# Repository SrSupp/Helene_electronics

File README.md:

Author: Sven Suppelt, Felix Herbst		Date: 09.05.2023

# HELENE - electronics for the low cost 6DOF robot
This repository is responsible for the electronics for the Helene robotarm. Included are the PCBs and the code to run on these. 

The robot arm has a motor control board on each of its 6 axes. The board of the lowest axis, the 1st axis, acts as ROS Serial Slave. All other axes receive their control data from the 1st axis via CAN. 

A single motor control board consists of a microcontroller (ESP32), a stepper motor driver (TMC5160), a magnetic encoder to determine the current position of the robot arm (AS5048) and a CAN transceiver. 
The 1st axis is equipped with an external magnetic encoder due to lack of space. All other axes have enough space so that the board can be mounted directly above the required magnet. 

# Folder structure
The boards are located in the folder "pcb". Here you will find the board for the external encoder and the motor control board. The source code for the boards can be found in the "code" folder. Stored there are the PlatformIO projects for the ROS Serial Slave (Helene_ESP_Master) and the other boards connected via CAN (Helene_ESP_Slave).
In the pcb folder there are two additional optional boards, the end effector board and a H-bridge with voltage converter. The end effector board has its own ESP32 with an ADC for measuring load cells. Furthermore, two outputs for servos are provided, so that grippers with integrated force measurement can be realized. The H-bridge is connected via the expansion ports on the boards and can drive motors up to 3A at 5V. It does not have its own microcontroller.

# System structure of the robot arm

# Available Serial Commands
Each slave is equipped with the possibility of serial communication. Via this interface the calibration value of each axis can be read and set and status information can be read out. It is absolutely necessary to calibrate each axis individually!
The following commands are available:

long form | short form | description
-------- | -------- | --------
*IDN? | IDN? | Prints identification
HELP? | HELP | Prints a help screen (not yet implemented)
CALSINGLEJOINT [joint ID] | CAJO [joint ID] | starts the calibration process of given joint. Instructions will be printed after that command!
SETNULL [0,1] | SENU [0,1] | globally enables (1) or disables (0) the Nullpunktfahrt at startup
GETCALVALUE [joint ID] | GECA [joint ID] | Prints the current saved calibration value of given joint
SETCALVALUE [joint ID] | SECA [joint ID] | Sets the current saved calibration value of given joint. Instructions are printed after that command!
GETACTUAL [joint ID] | GEAC [joint ID] | Prints the actual angle of given joint. The actual angle is: Raw_Angle - Calibration_Value
GETRAW [joint ID] | GERA [joint ID] | Prints the raw angle of given joint
DONULL [joint ID] | DONU [joint ID] | The given joint will do a Nullpunktfahrt
OFFANDNULL [joint ID] | OFNU [joint ID] | Sets a offset value on the current calibration value. After that a Nullpunktfahrt is initiated. Instructions are printed out!
DIAG | DIA | Prints out diagnose data

# Installation instructions

1. Gather all materials.
You will need 6 motor control boards and 1 external encoder board.
2. Do the wiring. 
You will have to run CAN and power to each motor control board. The boards are daisy-chainable!
3. Program the boards.
"Helene_ESP_Master" should be uploaded to the board in joint 1. This board is configured with rosserial so that it communicates directly with ROS.
"Helene_ESP_Slave" should be uploaded to the boards in joint 2-6. These boards talk via CAN to the board in Joint 1 and thus receive their control information. With each individual board it is possible to calibrate the robot arm. 
After programming, each board should slowly blink red!
4. Set the SMD-Jumpers.
For joints 1 and 6 the CAN terminating resistor must be set by bridging the SMD solder bridge next to the CAN sockets.
Additionally the Joint-ID must be set for each board. For this purpose four SMD pads are provided next to the USB socket. By bridging these pads the ID can be set. The data format is binary with the most significant bit first. For example the joint 5: 0 1 0 1 must be set. 
5. Calibrate the zero position
6. Enable Nullpunktfahrt globally

# Video installation instructions

The installation process is also explained in the following video.

Starting at 0:09 the installation of the electronics is explained. From 6:21 on the calibration is shown.

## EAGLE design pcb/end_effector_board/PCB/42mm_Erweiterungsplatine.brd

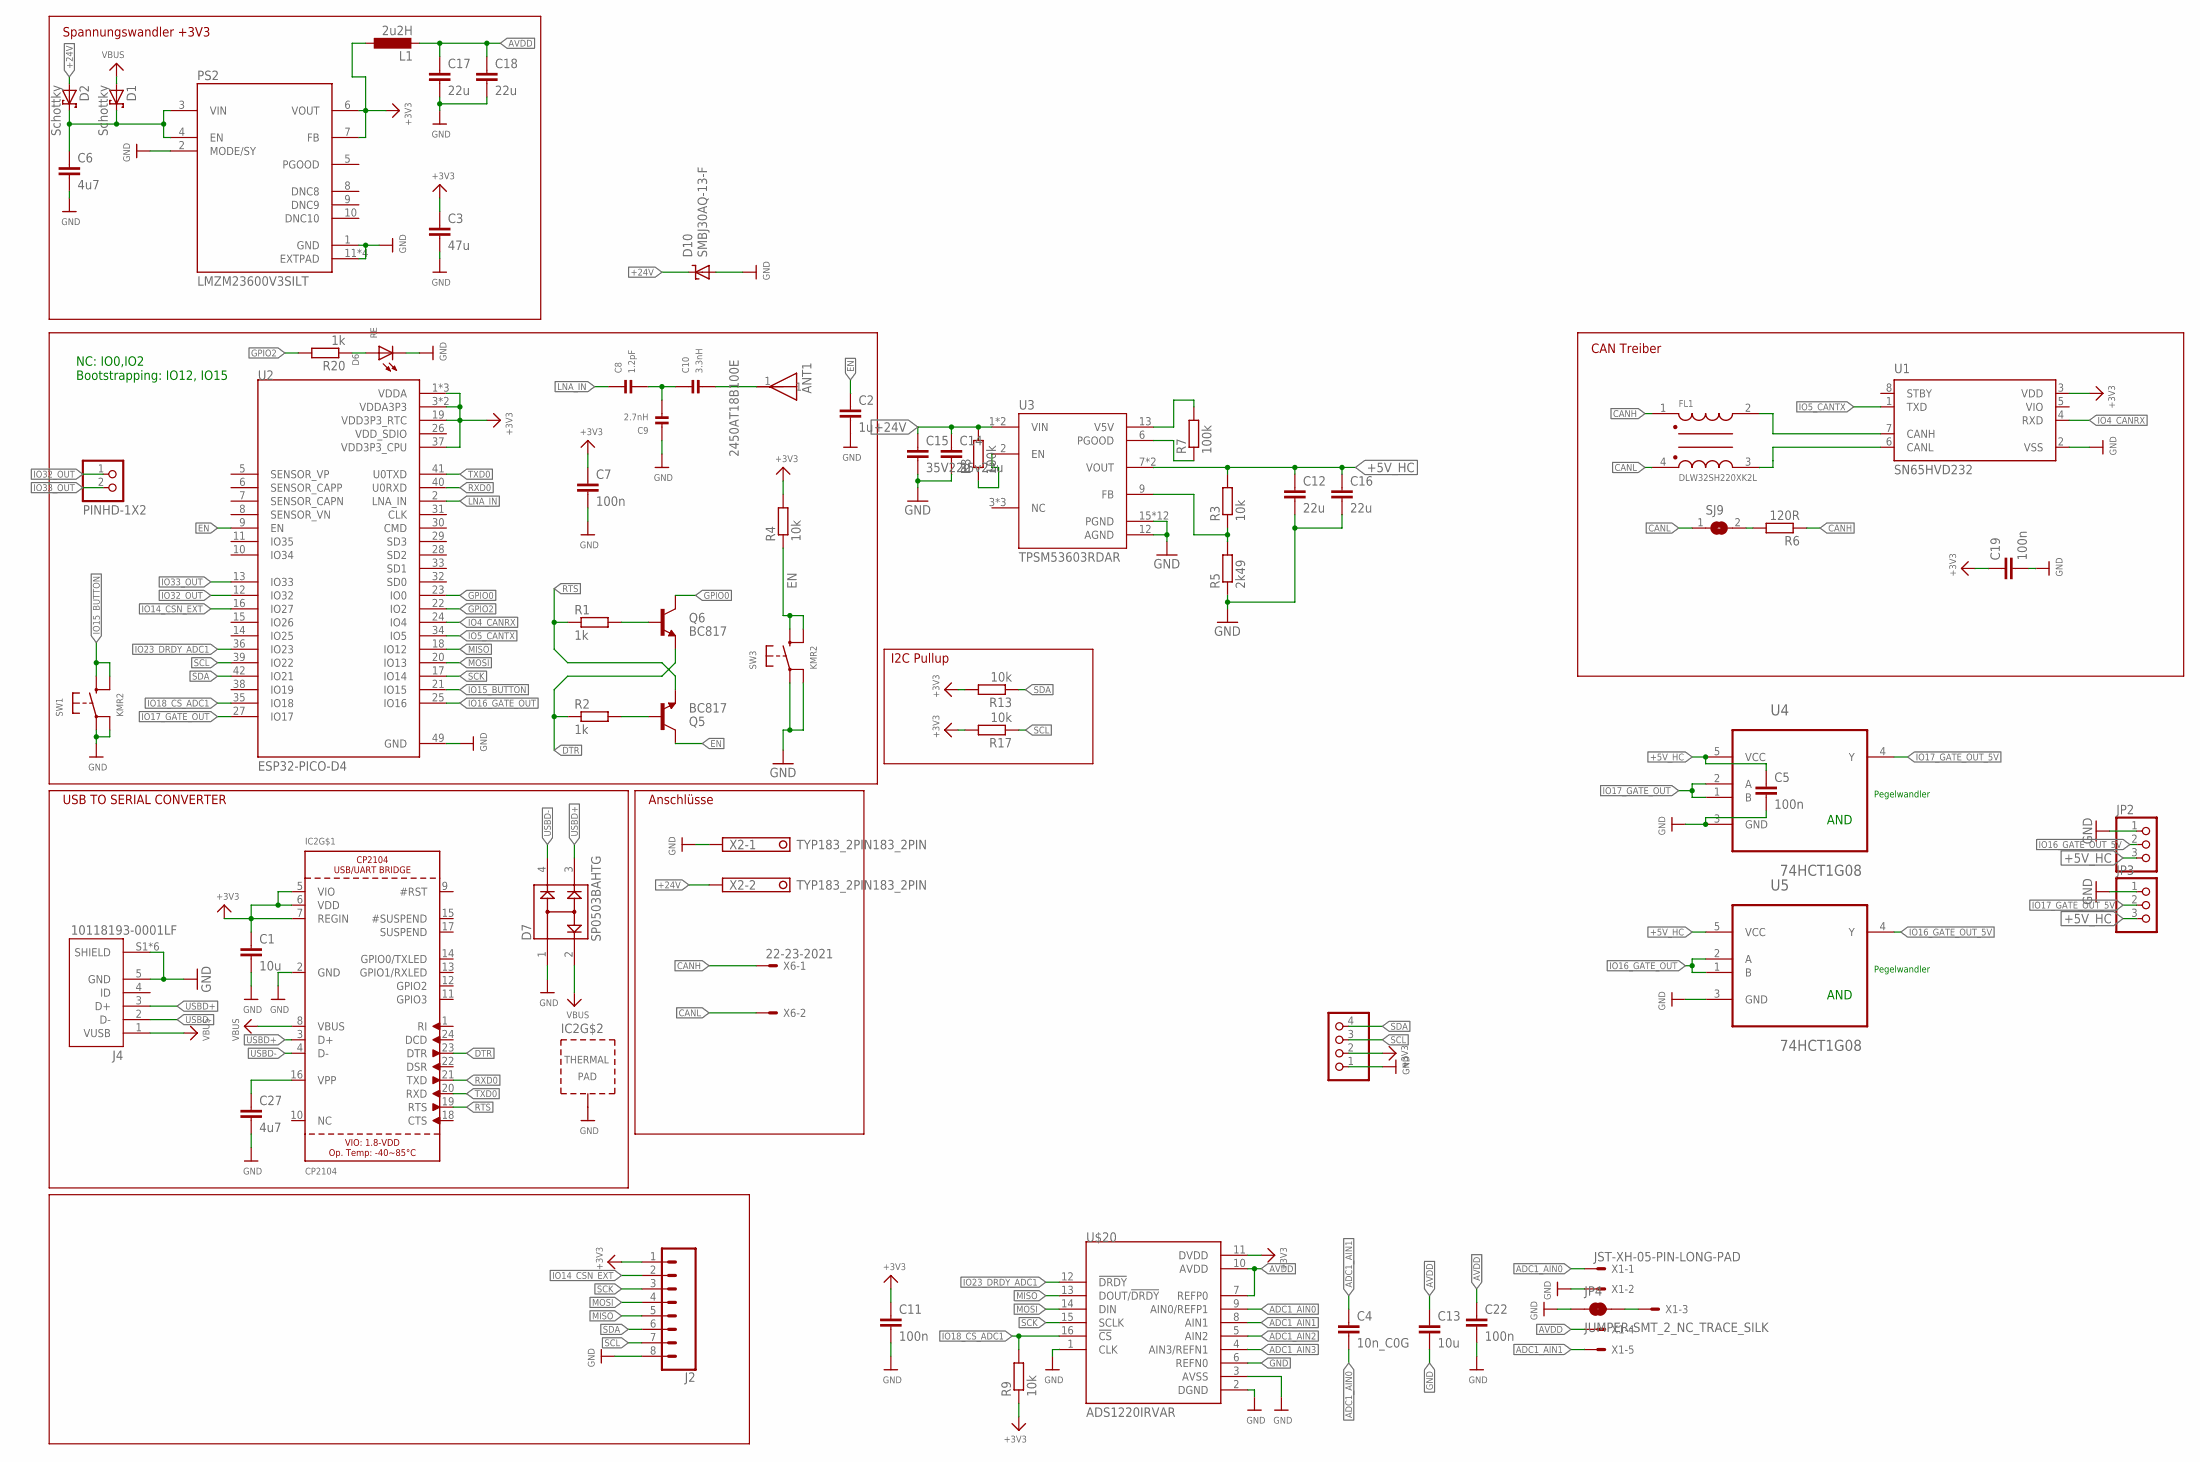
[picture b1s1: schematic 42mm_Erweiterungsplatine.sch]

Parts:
ANT1: 2450AT18B100E; ANT_2450AT18B100E
C1, C13: 10u; C0805
C2: 1u; C0805
C3: 47u; C0805
C4: 10n_C0G; C0805
C5, C7, C11, C19, C22: 100n; C0805
C6, C27: 4u7; C0805
C8: 1.2pF; _0402MP
C9: 2.7nH; _0402MP
C10: 3.3nH; _0402MP
C12, C16, C17, C18: 22u; C0805
C14: 35v22u; C1206
C15: 35V22u; C1206
D1, D2: Schottky; SMB
D6: RE; CHIP-LED0805
D7: SP0503BAHTG; SOT143
D10: SMBJ30AQ-13-F; SMBJ
FL1: DLW32SH220XK2L; FIL_DLW32SH110XK2L
IC2: CP2104; QFN24_4MM_SMSC
J2: CONN_08BM08B-SRSS-TB; BM08B-SRSS-TB
J4: 10118193-0001LF; FCI_10118193-0001LF
JP1: PINHD-1X4; 1X04
JP2, JP3: PINHD-1X3; 1X03
JP4: JUMPER-SMT_2_NC_TRACE_SILK; SMT-JUMPER_2_NC_TRACE_SILK
JP5: PINHD-1X2; 1X02
L1: 2u2H; L0805
PS2: LMZM23600V3SILT; CONV_LMZM23600V3SILT
Q5, Q6: BC817; SOT23-3
R1, R2, R20: 1k; R0805
R3, R4, R9, R13, R17: 10k; R0805
R5: 2k49; R0805
R6: 120R; R0805
R7, R8: 100k; R0805
SJ9: SJ
SW1, SW3: KMR2; BTN_KMR2_4.6X2.8
U1: SN65HVD232; SOIC127P600X175-8N
U2: ESP32-PICO-D4; PQFN50P700X700X104-49N
U3: TPSM53603RDAR; IC_TPSM53603RDAR
U4, U5: 74HCT1G08; SOT65P210X110-5N
U$20: ADS1220IRVAR; QFN50P350X350X100-17N214X214
X1: JST-XH-05-PIN-LONG-PAD; JST-XH-05-PACKAGE-LONG-PAD
X2: TYP183_2PIN183_2PIN; TYP183_FT_2PIN
X6: 22-23-2021

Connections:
3.3V: R9.1
+3V3: C1.1, C3.1, C7.1, C11.1, C19.1, IC2.5 (VIO), IC2.6 (VDD), IC2.7 (REGIN), J2.1, JP1.2, L1.1, PS2.6 (VOUT), PS2.7 (FB), R4.2, R13.2, R17.2, U1.3 (VDD), U2.1 (VDDA), U2.3 (VDDA3P3), U2.4 (VDDA3P3), U2.19 (VDD3P3_RTC), U2.37 (VDD3P3_CPU), U2.43 (VDDA), U2.46 (VDDA), U$20.11 (DVDD)
+5V_HC: C5.1, C12.1, C16.1, JP2.3, JP3.3, R3.2, U3.7 (VOUT), U3.8 (VOUT), U4.5 (VCC), U5.5 (VCC)
+24V: C14.1, C15.1, D2.A, D10.C, R8.2, U3.1 (VIN), U3.14 (VIN), X2.2
ADC1_AIN0: C4.2, U$20.9 (AIN0/REFP1), X1.1
ADC1_AIN1: C4.1, U$20.8 (AIN1), X1.5
ADC1_AIN2: U$20.5 (AIN2)
ADC1_AIN3: U$20.4 (AIN3/REFN1)
AVDD: C13.1, C17.1, C18.1, C22.1, L1.2, U$20.7 (REFP0), U$20.10 (AVDD), X1.4
CANH: FL1.1, R6.1, X6.1
CANL: FL1.4, SJ9.1, X6.2
DTR: IC2.23 (DTR), Q6.2 (E), R2.1
EN: C2.1, Q5.3 (C), R4.1, SW3.B (S), SW3.B' (S1), U2.9 (EN)
GND: C1.2, C2.2, C3.2, C5.2, C6.2, C7.2, C9.1, C11.2, C12.2, C13.2, C14.2, C15.2, C16.2, C17.2, C18.2, C19.2, C22.2, C27.2, D6.C, D7.1, D10.A, IC2.2 (GND), IC2.THERM (TP), J2.8, J4.5 (GND), J4.S1 (SHIELD), J4.S2 (SHIELD), J4.S3 (SHIELD), J4.S4 (SHIELD), J4.S5 (SHIELD), J4.S6 (SHIELD), JP1.1, JP2.1, JP3.1, JP4.1, PS2.1 (GND), PS2.2 (MODE/SY), PS2.11 (EXTPAD), PS2.11_1 (EXTPAD), PS2.11_2 (EXTPAD), PS2.11_3 (EXTPAD), R5.1, SW1.A, SW1.A' (P1), SW3.A, SW3.A' (P1), U1.2 (VSS), U2.49 (GND), U3.12 (AGND), U3.15 (PGND), U3.15_1 (PGND), U3.15_2 (PGND), U3.15_3 (PGND), U3.15_4 (PGND), U3.15_5 (PGND), U3.15_6 (PGND), U3.15_7 (PGND), U3.15_8 (PGND), U3.15_9 (PGND), U3.15_10 (PGND), U3.15_11 (PGND), U4.3 (GND), U5.3 (GND), U$20.1 (CLK), U$20.2 (DGND), U$20.3 (AVSS), U$20.6 (REFN0), X1.2, X2.1
GPIO0: Q6.3 (C), U2.23 (IO0)
GPIO2: R20.2, U2.22 (IO2)
IO4_CANRX: U1.4 (RXD), U2.24 (IO4)
IO5_CANTX: U1.1 (TXD), U2.34 (IO5)
IO14_CSN_EXT: J2.2, U2.16 (IO27)
IO15_BUTTON: SW1.B (S), SW1.B' (S1), U2.21 (IO15)
IO16_GATE_OUT: U2.25 (IO16), U5.1 (B), U5.2 (A)
IO16_GATE_OUT_5V: JP2.2, U5.4 (Y)
IO17_GATE_OUT: U2.27 (IO17), U4.1 (B), U4.2 (A)
IO17_GATE_OUT_5V: JP3.2, U4.4 (Y)
IO18_CS_ADC1: R9.2, U2.35 (IO18), U$20.16 (!CS)
IO23_DRDY_ADC1: U2.36 (IO23), U$20.12 (!DRDY)
IO32_OUT: JP5.1, U2.12 (IO32)
IO33_OUT: JP5.2, U2.13 (IO33)
LNA_IN: C8.1, U2.2 (LNA_IN)
MISO: J2.5, U2.18 (IO12), U$20.13 (DOUT/!DRDY)
MOSI: J2.4, U2.20 (IO13), U$20.14 (DIN)
unnamed: C6.1, D1.C, D2.C, PS2.3 (VIN), PS2.4 (EN)
unnamed: C8.2, C9.2, C10.1
unnamed: ANT1.1, C10.2
unnamed: R3.1, R5.2, U3.9 (FB)
unnamed: D6.A, R20.1
unnamed: R8.1, U3.2 (EN)
unnamed: JP4.2, X1.3
unnamed: FL1.2, U1.7 (CANH)
unnamed: FL1.3, U1.6 (CANL)
unnamed: Q5.1 (B), R2.2
unnamed: Q6.1 (B), R1.2
unnamed: R7.2, U3.13 (V5V)
unnamed: R7.1, U3.6 (PGOOD)
unnamed: R6.2, SJ9.2
unnamed: C27.1, IC2.16 (VPP)
RTS: IC2.19 (RTS), Q5.2 (E), R1.1
RXD0: IC2.21 (TXD), U2.40 (U0RXD)
SCK: J2.3, U2.17 (IO14), U$20.15 (SCLK)
SCL: J2.7, JP1.3, R17.1, U2.39 (IO22)
SDA: J2.6, JP1.4, R13.1, U2.42 (IO21)
TXD0: IC2.20 (RXD), U2.41 (U0TXD)
USBD+: D7.3, IC2.3 (D+), J4.3 (D+)
USBD-: D7.4, IC2.4 (D-), J4.2 (D-)
VBUS: D1.A, D7.2, IC2.8 (VBUS), J4.1 (VUSB)
VDD_SDIO: U2.26 (VDD_SDIO)
VIO: U1.5 (VIO)

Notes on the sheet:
USB TO SERIAL CONVERTER
NC: IO0,IO2 Bootstrapping: IO12, IO15
CAN Treiber
Anschlüsse
I2C Pullup
Spannungswandler +3V3
Pegelwandler
AND

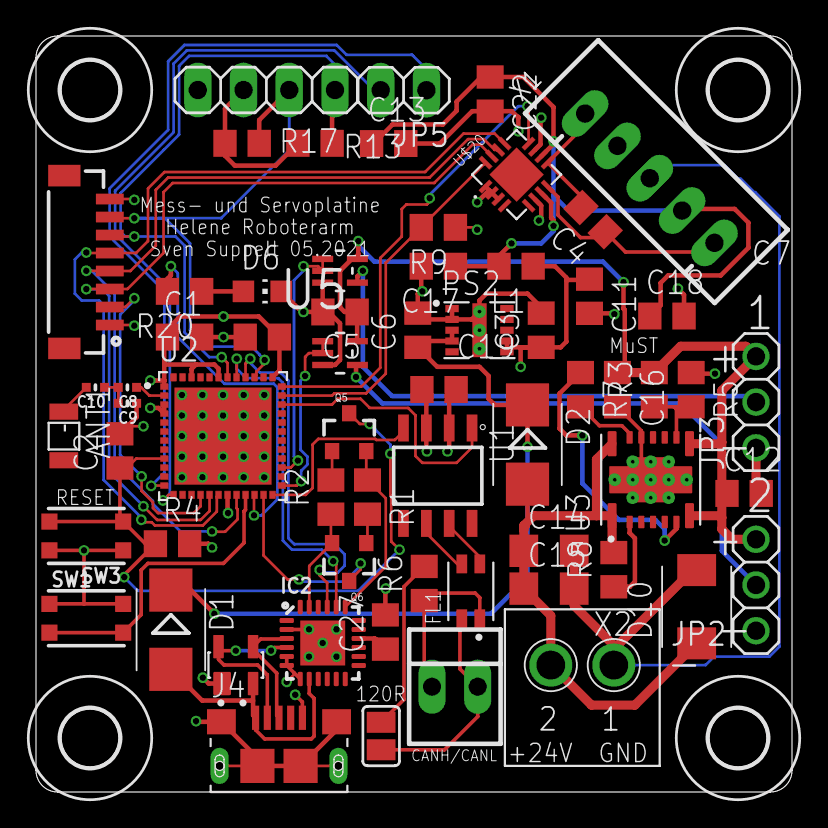
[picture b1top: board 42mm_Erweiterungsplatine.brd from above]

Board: 4 copper layers, 42.0 x 42.0 mm, 68 parts (1 on the bottom side), 52 nets.

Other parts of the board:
U$1, U$2, U$3, U$4: 3,2

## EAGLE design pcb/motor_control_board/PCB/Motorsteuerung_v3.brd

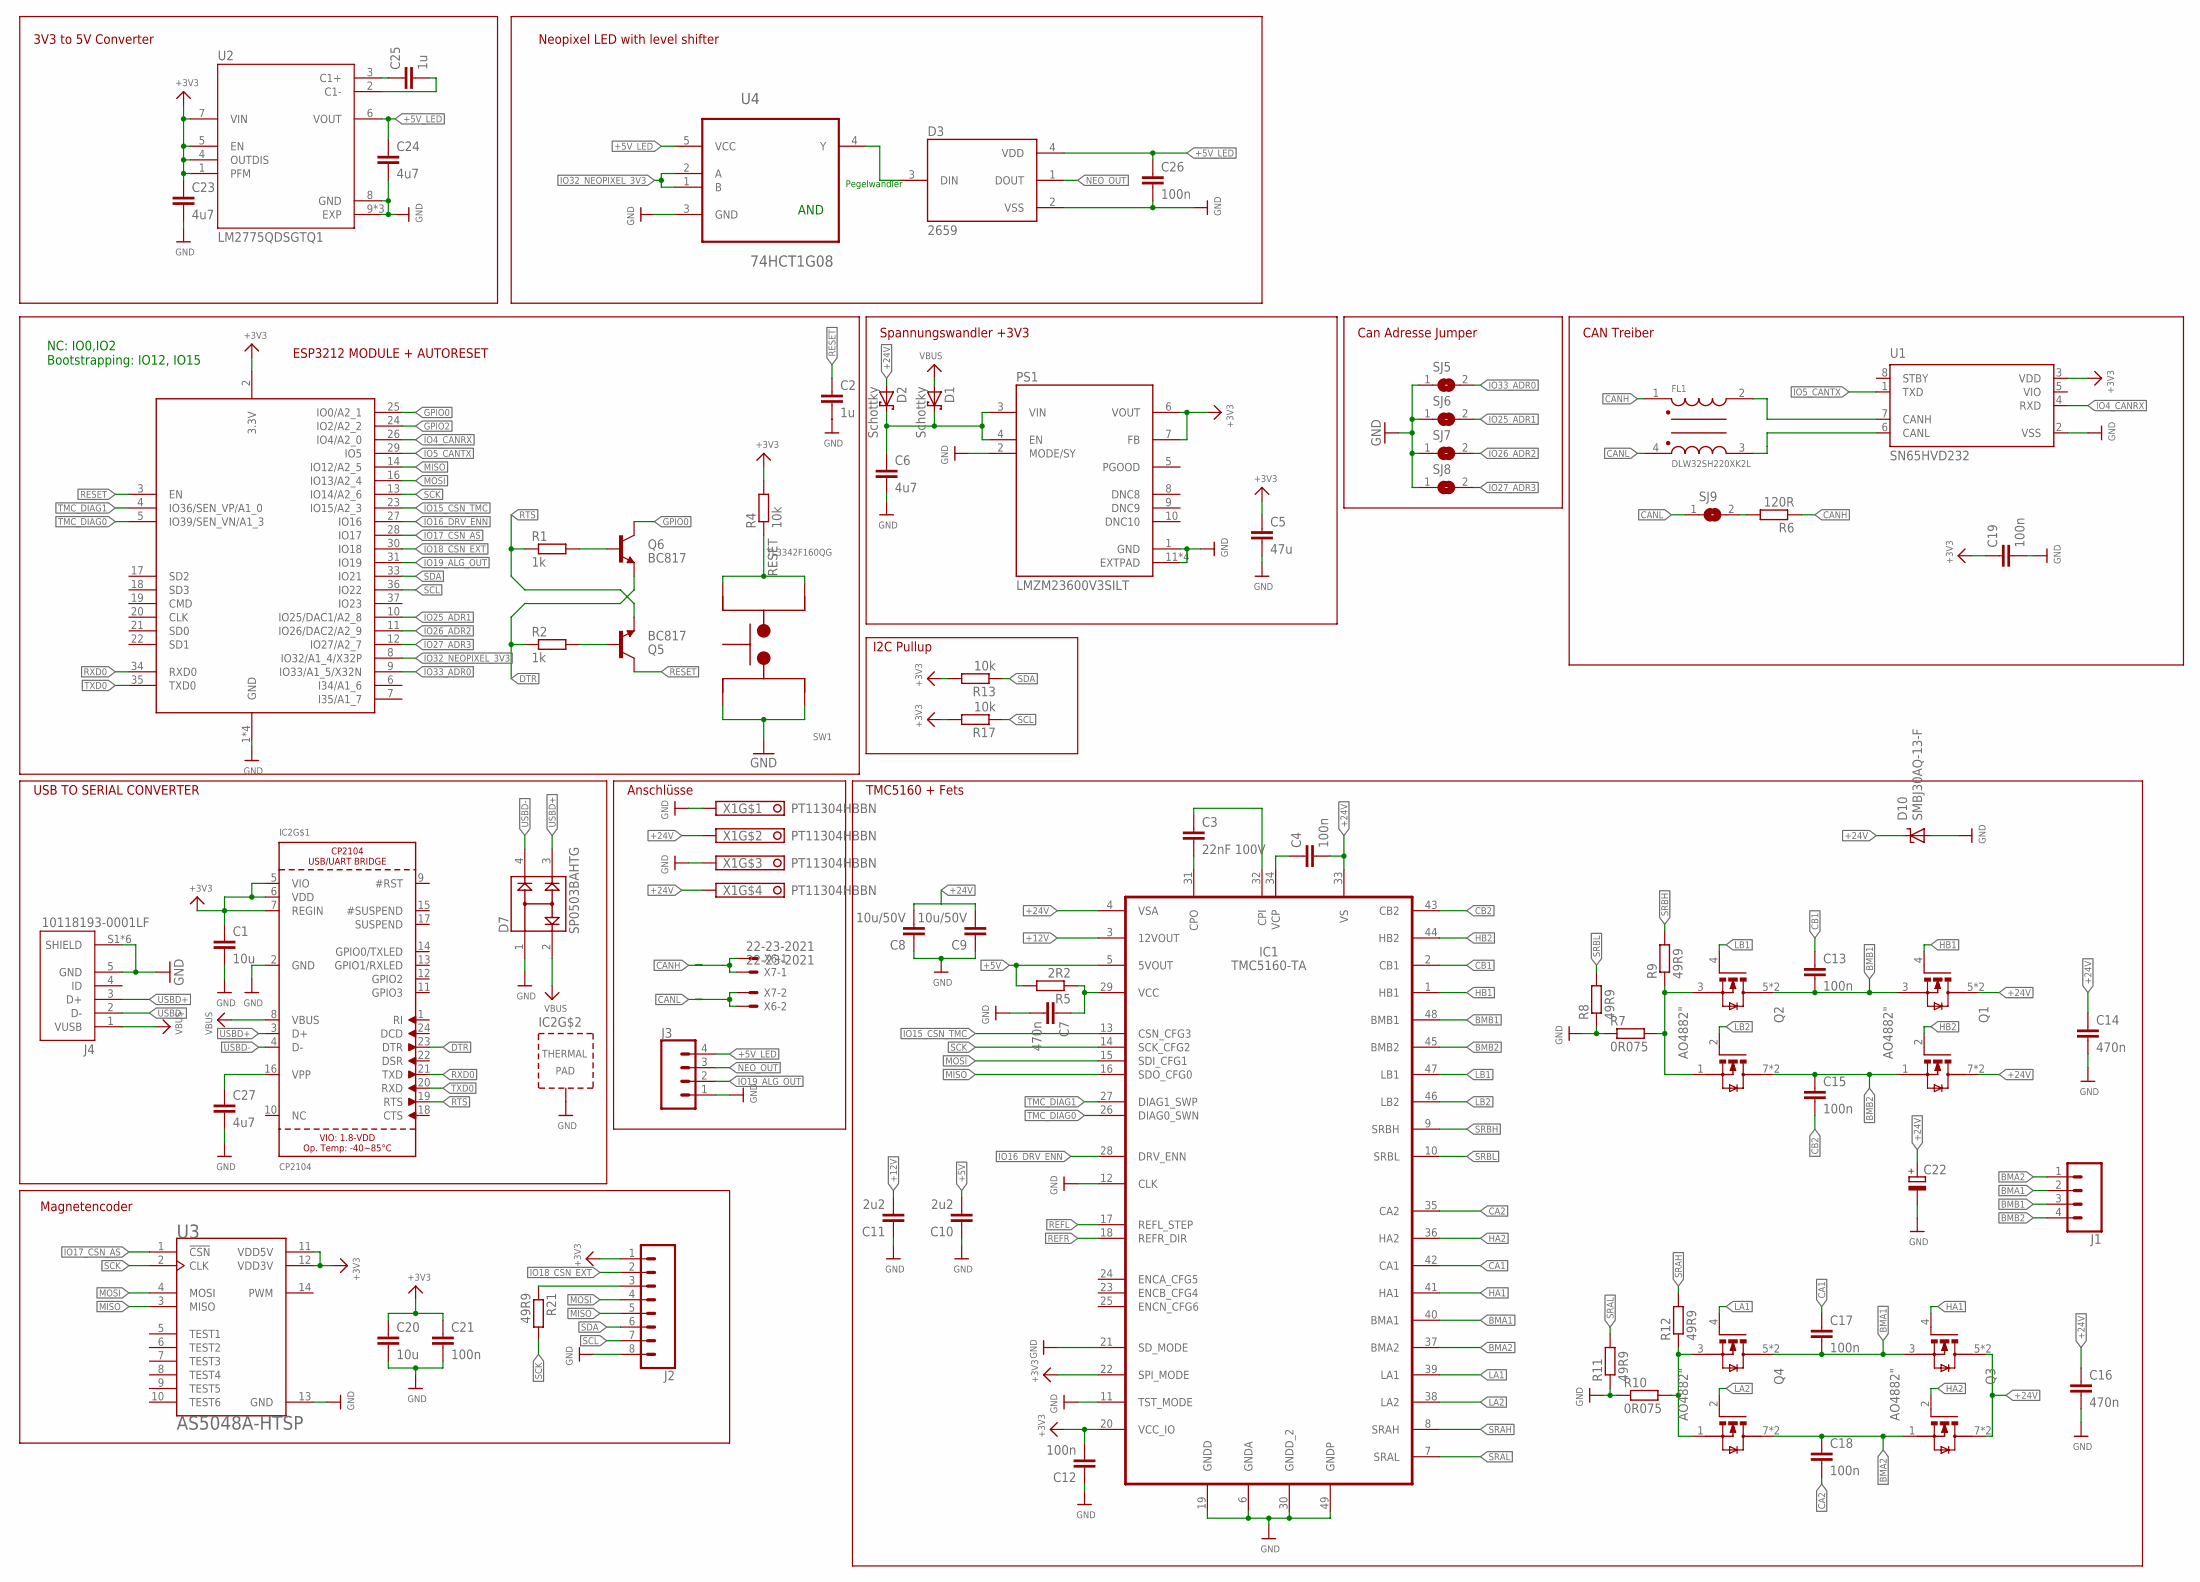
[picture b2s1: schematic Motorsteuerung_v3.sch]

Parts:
C1, C20: 10u; C0805
C2, C25: 1u; C0805
C3: 22nF 100V; C0805
C4, C12, C13, C15, C17, C18, C19, C21, C26: 100n; C0805
C5: 47u; C0805
C6, C23, C24, C27: 4u7; C0805
C7, C14, C16: 470n; C0805
C8, C9: 10u/50V; C0805
C10, C11: 2u2; C0805
C22: CPOL-EUE5-10.5; E5-10,5
D1, D2: Schottky; SMB
D3: 2659
D7: SP0503BAHTG; SOT143
D10: SMBJ30AQ-13-F; SMBJ
FL1: DLW32SH220XK2L; FIL_DLW32SH110XK2L
IC1: TMC5160-TA; TQFP48-EP
IC2: CP2104; QFN24_4MM_SMSC
J1: CONN_04; 1X04
J2: CONN_08BM08B-SRSS-TB; BM08B-SRSS-TB
J3: CONN_041.27MM; 1X04_1.27MM
J4: 10118193-0001LF; FCI_10118193-0001LF
PS1: LMZM23600V3SILT; CONV_LMZM23600V3SILT
Q1, Q2, Q3, Q4: AO4882"; SOIC8
Q5, Q6: BC817; SOT23-3
R1, R2: 1k; R0805
R4, R13, R17: 10k; R0805
R5: 2R2; R0805
R6: 120R; R0805
R7, R10: 0R075; R1206
R8, R9, R11, R12, R21: 49R9; R0805
SJ5, SJ6, SJ7, SJ8, SJ9: SJ
SW1: TL3342F160QG; SW_TL3342F160QG
U1: SN65HVD232; SOIC127P600X175-8N
U2: LM2775QDSGTQ1; SON50P200X200X80-9N
U3: AS5048A-HTSP; SOP65P640X120-14N
U4: 74HCT1G08; SOT65P210X110-5N
X1: PT11304HBBN; TYP184_FT
X2: ESP32_WROOM32_SKINNY; WROOM32_SKINNY
X6, X7: 22-23-2021

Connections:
+3V3: C1.1, C5.1, C12.2, C19.1, C20.1, C21.1, C23.1, IC1.20 (VCC_IO), IC1.22 (SPI_MODE), IC2.5 (VIO), IC2.6 (VDD), IC2.7 (REGIN), J2.1, PS1.6 (VOUT), PS1.7 (FB), R4.2, R13.2, R17.2, U1.3 (VDD), U2.1 (PFM), U2.4 (OUTDIS), U2.5 (EN), U2.7 (VIN), U3.11 (VDD5V), U3.12 (VDD3V), X2.2 (3.3V)
+5V: C10.2, IC1.5 (5VOUT), R5.2
+5V_LED: C24.1, C26.1, D3.4 (VDD), J3.4, U2.6 (VOUT), U4.5 (VCC)
+12V: C11.2, IC1.3 (12VOUT)
+24V: C4.2, C8.2, C9.2, C14.1, C16.1, C22.+, D2.A, D10.C, IC1.4 (VSA), IC1.33 (VS), Q1.5 (D1), Q1.6 (D1), Q1.7 (D2), Q1.8 (D2), Q3.5 (D1), Q3.6 (D1), Q3.7 (D2), Q3.8 (D2), X1.2, X1.4
BMA1: C17.2, IC1.40 (BMA1), J1.2, Q3.3 (S1), Q4.5 (D1), Q4.6 (D1)
BMA2: C18.1, IC1.37 (BMA2), J1.1, Q3.1 (S2), Q4.7 (D2), Q4.8 (D2)
BMB1: C13.2, IC1.48 (BMB1), J1.3, Q1.3 (S1), Q2.5 (D1), Q2.6 (D1)
BMB2: C15.1, IC1.45 (BMB2), J1.4, Q1.1 (S2), Q2.7 (D2), Q2.8 (D2)
CA1: C17.1, IC1.42 (CA1)
CA2: C18.2, IC1.35 (CA2)
CANH: FL1.1, R6.1, X6.1, X7.1
CANL: FL1.4, SJ9.1, X6.2, X7.2
CB1: C13.1, IC1.2 (CB1)
CB2: C15.2, IC1.43 (CB2)
DTR: IC2.23 (DTR), Q6.2 (E), R2.1
GND: C1.2, C2.2, C5.2, C6.2, C7.2, C8.1, C9.1, C10.1, C11.1, C12.1, C14.2, C16.2, C19.2, C20.2, C21.2, C22.-, C23.2, C24.2, C26.2, C27.2, D3.2 (VSS), D7.1, D10.A, IC1.6 (GNDA), IC1.11 (TST_MODE), IC1.12 (CLK), IC1.19 (GNDD), IC1.21 (SD_MODE), IC1.30 (GNDD_2), IC1.49 (GNDP), IC2.2 (GND), IC2.THERM (TP), J2.8, J3.1, J4.5 (GND), J4.S1 (SHIELD), J4.S2 (SHIELD), J4.S3 (SHIELD), J4.S4 (SHIELD), J4.S5 (SHIELD), J4.S6 (SHIELD), PS1.1 (GND), PS1.2 (MODE/SY), PS1.11 (EXTPAD), PS1.11_1 (EXTPAD), PS1.11_2 (EXTPAD), PS1.11_3 (EXTPAD), R7.1, R8.1, R10.1, R11.1, SJ5.1, SJ6.1, SJ7.1, SJ8.1, SW1.3, SW1.4, U1.2 (VSS), U2.8 (GND), U2.9 (EXP), U2.9_1 (EXP), U2.9_2 (EXP), U3.13 (GND), U4.3 (GND), X1.1, X1.3, X2.1 (GND), X2.15 (GND), X2.38 (GND), X2.P$1 (GND)
GPIO0: Q6.3 (C), X2.25 (IO0/A2_1)
GPIO2: X2.24 (IO2/A2_2)
HA1: IC1.41 (HA1), Q3.4 (G1)
HA2: IC1.36 (HA2), Q3.2 (G2)
HB1: IC1.1 (HB1), Q1.4 (G1)
HB2: IC1.44 (HB2), Q1.2 (G2)
IO4_CANRX: U1.4 (RXD), X2.26 (IO4/A2_0)
IO5_CANTX: U1.1 (TXD), X2.29 (IO5)
IO15_CSN_TMC: IC1.13 (CSN_CFG3), X2.23 (IO15/A2_3)
IO16_DRV_ENN: IC1.28 (DRV_ENN), X2.27 (IO16)
IO17_CSN_AS: U3.1 (!CSN), X2.28 (IO17)
IO18_CSN_EXT: J2.2, X2.30 (IO18)
IO19_ALG_OUT: J3.2, X2.31 (IO19)
IO25_ADR1: SJ6.2, X2.10 (IO25/DAC1/A2_8)
IO26_ADR2: SJ7.2, X2.11 (IO26/DAC2/A2_9)
IO27_ADR3: SJ8.2, X2.12 (IO27/A2_7)
IO32_NEOPIXEL_3V3: U4.1 (B), U4.2 (A), X2.8 (IO32/A1_4/X32P)
IO33_ADR0: SJ5.2, X2.9 (IO33/A1_5/X32N)
LA1: IC1.39 (LA1), Q4.4 (G1)
LA2: IC1.38 (LA2), Q4.2 (G2)
LB1: IC1.47 (LB1), Q2.4 (G1)
LB2: IC1.46 (LB2), Q2.2 (G2)
MISO: IC1.16 (SDO_CFG0), J2.5, U3.3 (MISO), X2.14 (IO12/A2_5)
MOSI: IC1.15 (SDI_CFG1), J2.4, U3.4 (MOSI), X2.16 (IO13/A2_4)
unnamed: C25.1, U2.3 (C1+)
unnamed: C6.1, D1.C, D2.C, PS1.3 (VIN), PS1.4 (EN)
unnamed: C3.2, IC1.31 (CPO)
unnamed: C3.1, IC1.32 (CPI)
unnamed: C4.1, IC1.34 (VCP)
unnamed: C25.2, U2.2 (C1-)
unnamed: C7.1, IC1.29 (VCC), R5.1
unnamed: FL1.2, U1.7 (CANH)
unnamed: Q4.1 (S2), Q4.3 (S1), R10.2, R12.1
unnamed: Q2.1 (S2), Q2.3 (S1), R7.2, R9.1
unnamed: FL1.3, U1.6 (CANL)
unnamed: Q5.1 (B), R2.2
unnamed: Q6.1 (B), R1.2
unnamed: D3.3 (DIN), U4.4 (Y)
unnamed: R6.2, SJ9.2
unnamed: J2.3, R21.1
unnamed: C27.1, IC2.16 (VPP)
NEO_OUT: D3.1 (DOUT), J3.3
REFL: IC1.17 (REFL_STEP)
REFR: IC1.18 (REFR_DIR)
RESET: C2.1, Q5.3 (C), R4.1, SW1.1, SW1.2, X2.3 (EN)
RTS: IC2.19 (RTS), Q5.2 (E), R1.1
RXD0: IC2.21 (TXD), X2.34 (RXD0)
SCK: IC1.14 (SCK_CFG2), R21.2, U3.2 (CLK), X2.13 (IO14/A2_6)
SCL: J2.7, R17.1, X2.36 (IO22)
SDA: J2.6, R13.1, X2.33 (IO21)
SRAH: IC1.8 (SRAH), R12.2
SRAL: IC1.7 (SRAL), R11.2
SRBH: IC1.9 (SRBH), R9.2
SRBL: IC1.10 (SRBL), R8.2
TMC_DIAG0: IC1.26 (DIAG0_SWN), X2.5 (IO39/SEN_VN/A1_3)
TMC_DIAG1: IC1.27 (DIAG1_SWP), X2.4 (IO36/SEN_VP/A1_0)
TXD0: IC2.20 (RXD), X2.35 (TXD0)
USBD+: D7.3, IC2.3 (D+), J4.3 (D+)
USBD-: D7.4, IC2.4 (D-), J4.2 (D-)
VBUS: D1.A, D7.2, IC2.8 (VBUS), J4.1 (VUSB)
VIO: U1.5 (VIO)

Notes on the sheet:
USB TO SERIAL CONVERTER
ESP3212 MODULE + AUTORESET
NC: IO0,IO2 Bootstrapping: IO12, IO15
Spannungswandler +3V3
CAN Treiber
Anschlüsse
TMC5160 + Fets
Magnetencoder
Can Adresse Jumper
I2C Pullup
Pegelwandler
AND
3V3 to 5V Converter
Neopixel LED with level shifter

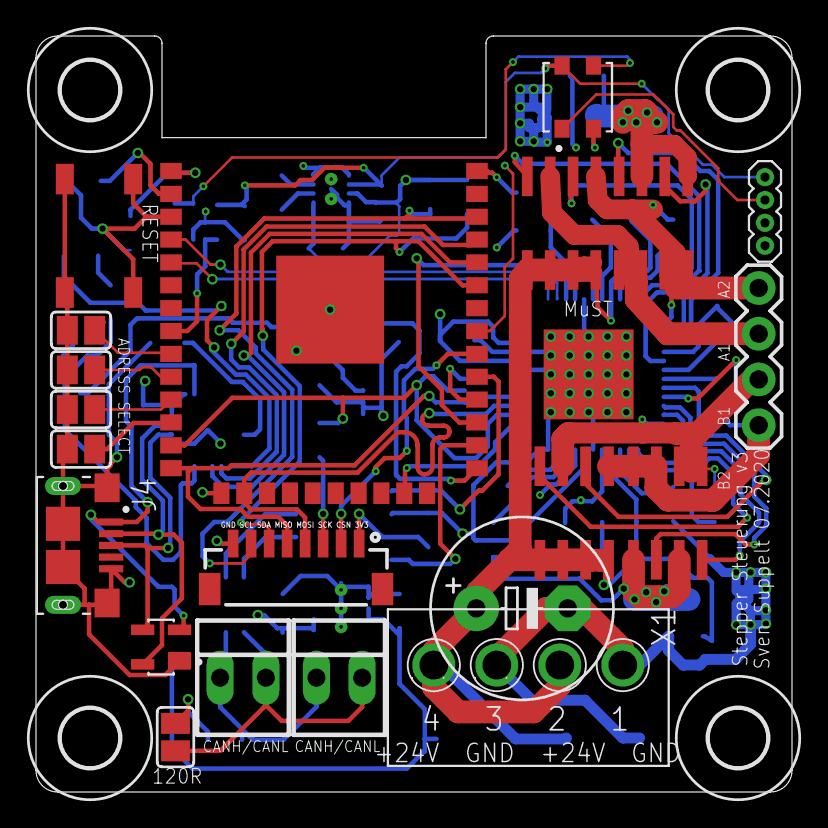
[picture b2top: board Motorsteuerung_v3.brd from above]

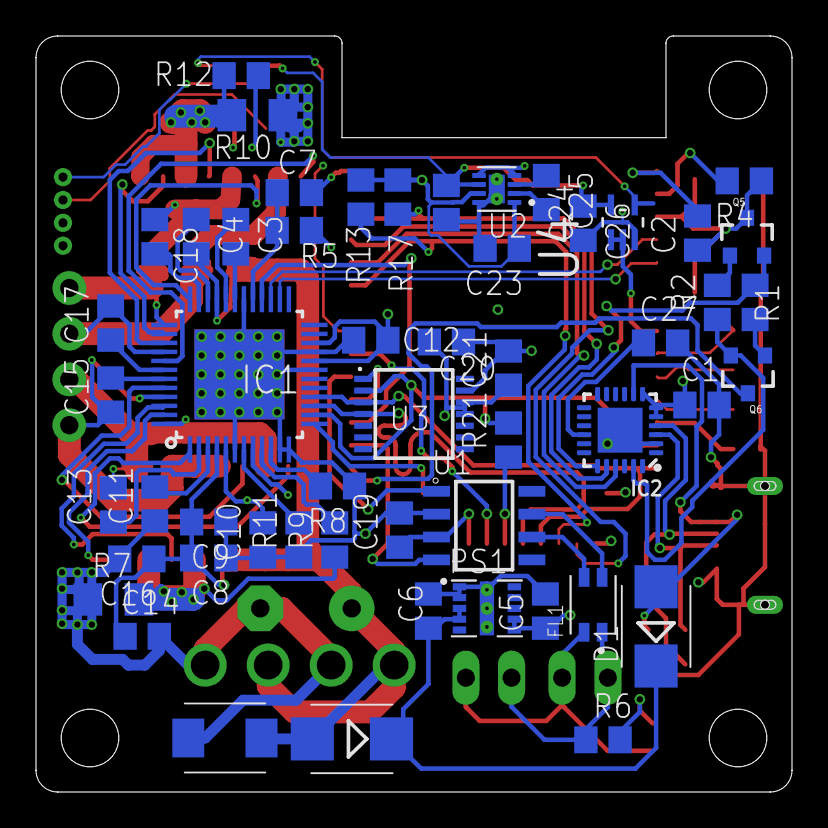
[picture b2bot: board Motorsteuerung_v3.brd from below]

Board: 4 copper layers, 42.0 x 42.0 mm, 78 parts (53 on the bottom side), 74 nets.

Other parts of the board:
U$1, U$2, U$3, U$4: 3,2

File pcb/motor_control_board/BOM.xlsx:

|  |  | Motorsteuerung V3 BOM
Item # | *Designator | *Qty | Manufacturer | *Mfg Part # | Description / Value | *Package/Footprint | Type | Your Instructions / Notes
1 | C1, C20 | 2 | Murata | GRM21BR6YA106KE43L | 10uF 0805 min.5V | 0805 | SMD
2 | C2, C25 | 2 | KEMET | C0805C105K4RAC7210 | 1uF 0805 min. 5V | 0805 | SMD
3 | C3 | 1 | Yageo | CC0805KRX7R0BB223 | 22nF 0805 100V | 0805 | SMD
4 | C4, C12, C13, C15, C17, C18, C19, C21, C26 | 9 | KEMET | C0805C104J5RACAUTO | 100nF 0805 | 0805 | SMD
5 | C5 | 1 | Taiyo Yuden | JMK212BJ476MG-T | 47uF 0805 min 4V | 0805 | SMD
6 | C6, C23, C24, C27 | 4 | Taiyo Yuden | UMK212BBJ475MG-T | 4,7uF 0805 min 5V | 0805 | SMD
7 | C7, C14, C16 | 3 | KEMET | C0805C474K5RAC7210 | 470nF 0805 min 25V | 0805 | SMD
8 | C8, C9 | 2 | Murata | GRM21BR6YA106KE43L | 10uF 0805 min 25V | 0805 | SMD
9 | C10, C11 | 2 | Taiyo Yuden | UMK212ABJ225KG-T | 2,2uF 0805 min 12V | 0805 | SMD
10 | C22 | 1 | Do not equip | Do not equip | Do not equip | Do not equip | THT | Do not equip
11 | R1, R2 | 2 | Yageo | RC0805FR-071KL | 1k 0805 | 0805 | SMD
12 | R4, R13, R17 | 3 | Yageo | RC0805JR-0710KL | 10k 0805 | 0805 | SMD
13 | R5 | 1 | CR0805-J/-2R2ELF | Bourns | 2,2 Ohm 0805 | 0805 | SMD
14 | R6 | 1 | Yageo | RC0805FR-07120RL | 120 Ohm 0805 | 0805 | SMD
15 | R7, R10 | 2 | Yageo | RL1206FR-070R075L | 75mOhm 1206 | 1206 | SMD | Messshunt
16 | R8, R9, R11, R12, R21 | 5 | Panasonic | ERA-6AEB49R9V | 49,9 Ohm 0805 | 0805 | SMD
17 | D1, D2 | 2 | Multicomp | SS34A | SMB Shottky Diode | SMB | SMD
18 | D3 | 1 | Adafruit Industries | 2659 | 2659 Adafruit LED | 2659 | SMD
19 | D7 | 1 | Littlefuse | SP0503BAHTG | USB ESD Schutz | SOT143 | SMD
20 | D10 | 1 | Diodes Inc. | SMBJ30AQ-13-F | TVS Diode | SMBJ | SMD
21 | IC1 | 1 | Trinamic | TMC5160-TA-T | Motortreiber IC | TQFP48-EP | SMD
22 | IC2 | 1 | Solicon Labs | CP2104-F03-GM | USB Seriell Wandler | QFN24_4MM_SMSC | SMD
23 | J1 | 1 | Do not equip | Do not equip | Do not equip | Do not equip | THT
24 | J2 | 1 | JST | BM08B-SRSS-TB(LF)(SN) | 8 Port SMD stehende Buchse |  | SMD
25 | J3 | 1 | Do not equip | Do not equip | Do not equip | Do not equip | THT
27 | J4 | 1 | Amphenol FCI | 10118193-0001LF | USB-Stecker 5P MICRO USB TYPE B RECEPTACLE W/ PEGS | FCI_10118193-0001LF | SMD
28 | PS1 | 1 | Texas Instruments | LMZM23600V3SILR | 3,3V Spannungswandler |  | SMD
29 | Q1, Q2, Q3, Q4 | 4 | Alpha&Omega | AO4882 | Dual N-Ch Mosfet | SOIC8 | SMD
30 | Q5, Q6 | 2 | ON Semiconductor | BC817-16LT1G | NPN Transistor | SOT23-3 | SMD
31 | SJ1, SJ2 | 2 | Do not equip | Do not equip | Do not equip | Do not equip | SMD | Do not equip
32 | SJ5, SJ6, SJ7, SJ8, SJ9 | 5 | Do not equip | Do not equip | Do not equip | Do not equip | SMD | Do not equip
33 | SW1 | 1 | E-Switch | TL3342F160QG | Taster |  | SMD
34 | U1 | 1 | Texas Instruments | SN65HVD232DR | Can Treiber | SOIC127P600X175-8N | SMD
35 | U2 | 1 | Texas Instruments | LM2775QDSGTQ1 | 3,3V zu 5v | SON50P200X200X80-9N | SMD
36 | U3 | 1 | ams | AS5048A-HTSP-500 | Magnetencoder | SOP65P640X120-14N | SMD
37 | U4 | 1 | Nexperia | 74LVC1G08GW,125 | And Gate | SOT65P210X110-5N | SMD
38 | X1 | 1 | Do not equip | Do not equip | Do not equip | Do not equip | THT | Do not equip
39 | X2 | 1 | Espressif Systems | ESP32-WROOM-32 | Microprozessor |  | SMD
40 | X6, X7 | 2 | Do not equip | Do not equip | Do not equip | Do not equip | THT | Do not equip
41 | FL1 | 1 | Murata | DLW32SH220XK2L | Gleichtaktdrosseln / Filter 1210 80VDC 22uH 250mA AEC-Q200 | 1210 | SMD

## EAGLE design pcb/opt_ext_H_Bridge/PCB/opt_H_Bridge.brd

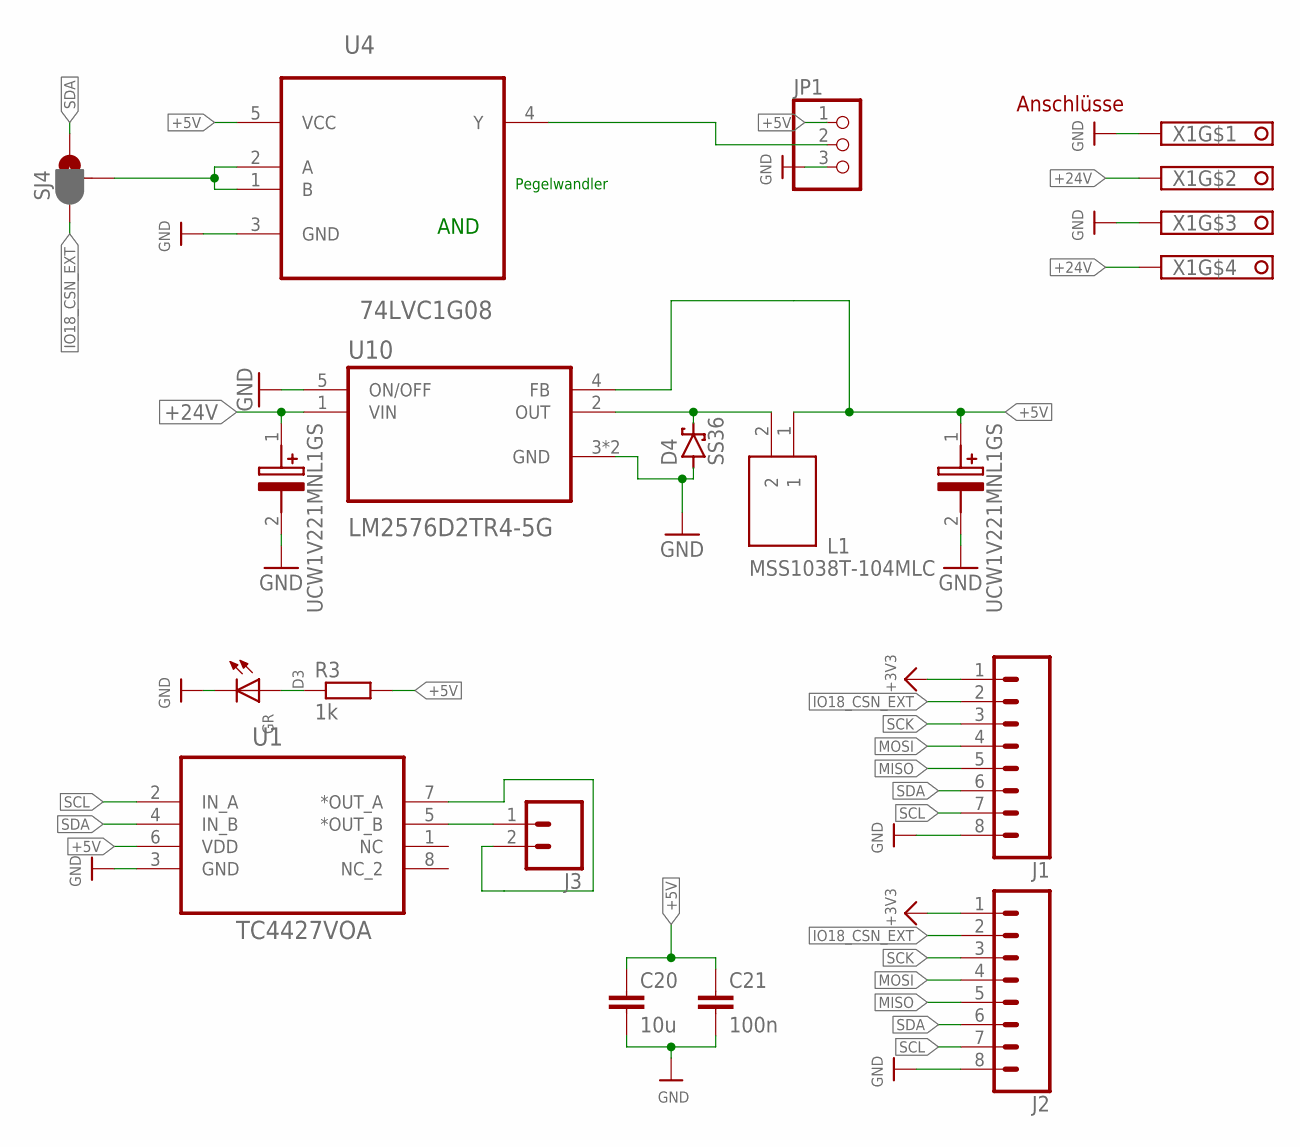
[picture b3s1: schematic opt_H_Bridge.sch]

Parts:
C1, C31: UCW1V221MNL1GS; UWT(8X10)
C20: 10u; C0805
C21: 100n; C0805
D3: GR; CHIP-LED0805
D4: SS36; SMC
J1, J2: CONN_08BM08B-SRSS-TB; BM08B-SRSS-TB
J3: CONN_023.5MM; SCREWTERMINAL-3.5MM-2
JP1: PINHD-1X3; 1X03
L1: MSS1038T-104MLC; INDPM102100X400N
R3: 1k; R0805
SJ4: JUMPER_PAD-3-1&2_NC_BY_PASTE; PAD-HUMPER-3-1&2_NC_BY_PASTE_YES_SILK_FULL_BOX
U1: TC4427VOA; SOIC127P600X175-8N
U4: 74LVC1G08; SOT65P210X110-5N
U10: LM2576D2TR4-5G; VREG_TPS79625KTTR
X1: PT11304HBBN; TYP184_FT

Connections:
+3V3: J1.1, J2.1
+5V: C1.1 (+), C20.1, C21.1, JP1.1, L1.1, R3.2, U1.6 (VDD), U4.5 (VCC), U10.4 (FB)
+24V: C31.1 (+), U10.1 (VIN), X1.2, X1.4
GND: C1.2 (-), C20.2, C21.2, C31.2 (-), D3.C, D4.A, J1.8, J2.8, JP1.3, U1.3 (GND), U4.3 (GND), U10.3 (GND), U10.5 (ON/OFF), U10.6 (GND), X1.1, X1.3
IO18_CSN_EXT: J1.2, J2.2, SJ4.1
MISO: J1.5, J2.5
MOSI: J1.4, J2.4
unnamed: J3.1, U1.5 (*OUT_B)
unnamed: J3.2, U1.7 (*OUT_A)
unnamed: JP1.2, U4.4 (Y)
unnamed: SJ4.2, U4.1 (B), U4.2 (A)
unnamed: D3.A, R3.1
unnamed: D4.C, L1.2, U10.2 (OUT)
SCK: J1.3, J2.3
SCL: J1.7, J2.7, U1.2 (IN_A)
SDA: J1.6, J2.6, SJ4.3, U1.4 (IN_B)

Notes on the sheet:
Anschlüsse
Pegelwandler
AND

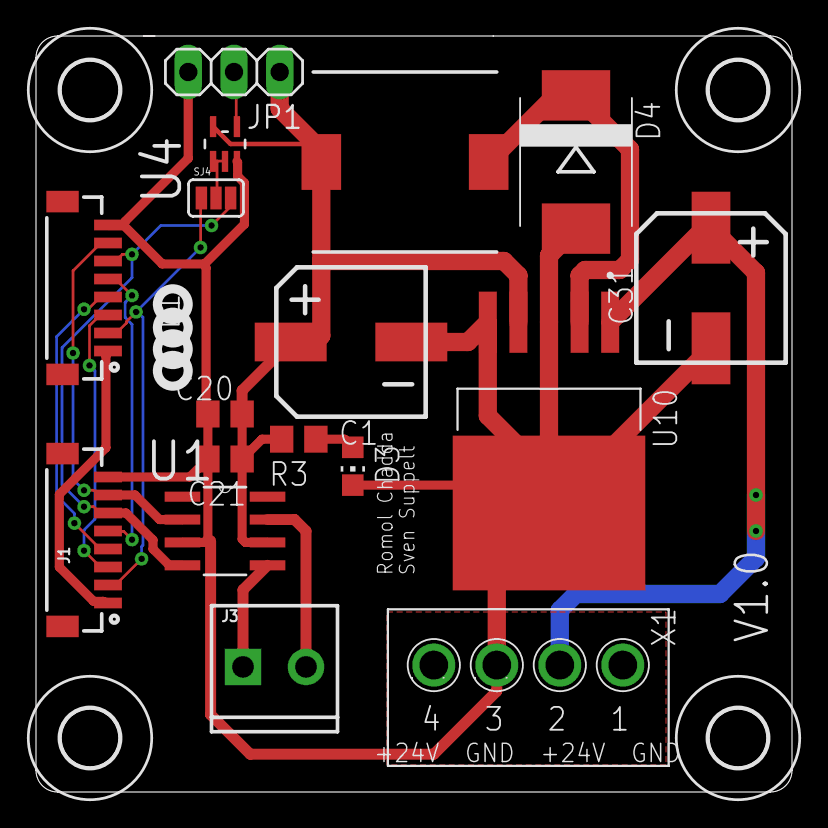
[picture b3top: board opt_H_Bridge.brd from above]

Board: 2 copper layers, 42.0 x 42.0 mm, 21 parts (0 on the bottom side), 16 nets.

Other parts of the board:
U$1, U$2, U$3, U$4: 3,2

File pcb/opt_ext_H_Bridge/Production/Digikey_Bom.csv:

"Manufacturer Part Number","Manufacturer","Digi-Key Part Number","Customer Reference","Reference Designator","Packaging","Part Status","Quantity","Unit Price","Extended Price","Quantity Available","Mfg Std Lead Time","Description","RoHS Status","Lead Free Status","REACH Status"
"74LVC1G08GW,125","Nexperia USA Inc.","1727-2872-1-ND","","","Cut Tape (CT)","Active","1","0,18000","0,18 €","27759","4 Weeks","IC GATE AND 1CH 2-INP 5TSSOP","ROHS3 Compliant","Lead free","REACH Unaffected"
"BM08B-SRSS-TB(LF)(SN)","JST Sales America Inc.","455-1794-1-ND","","","Cut Tape (CT)","Active","2","0,72000","1,44 €","12416","16 Weeks","CONN HEADER SMD 8POS 1MM","RoHS Compliant","Lead free","Not Available"
"LM2576D2TR4-5G","ON Semiconductor","LM2576D2TR4-5GOSCT-ND","","","Cut Tape (CT)","Active","1","1,97000","1,97 €","1873","9 Weeks","IC REG MULTI CONFG 5V 3A D2PAK-5","ROHS3 Compliant","Lead free","REACH Unaffected"
"SS36-E3/57T","Vishay Semiconductor Diodes Division","SS36-E3/57TGICT-ND","","","Cut Tape (CT)","Active","1","0,43000","0,43 €","11334","8 Weeks","DIODE SCHOTTKY 60V 3A DO214AB","ROHS3 Compliant","Lead free","REACH Unaffected"
"UCW1V221MNL1GS","Nichicon","493-9430-1-ND","","","Cut Tape (CT)","Active","2","0,60000","1,20 €","28323","16 Weeks","CAP ALUM 220UF 20% 35V SMD","ROHS3 Compliant","Lead free","REACH Unaffected"
"TC4427VOA713","Microchip Technology","TC4427VOA713CT-ND","","","Cut Tape (CT)","Active","2","1,12000","2,24 €","1871","8 Weeks","IC GATE DRVR LOW-SIDE 8SOIC","ROHS3 Compliant","Lead free","REACH Unaffected"
"1984617","Phoenix Contact","277-1721-ND","","","Box","Active","1","0,41000","0,41 €","12907","7 Weeks","TERM BLK 2POS SIDE ENT 3.5MM PCB","RoHS Compliant","Lead free","Not Available"
"A08SR08SR30K152A","JST Sales America Inc.","455-3004-ND","","","Bulk","Active","1","1,63000","1,63 €","1113","12 Weeks","JUMPER 08SR-3S - 08SR-3S 6""","RoHS Compliant","Lead free","Not Available"
"CDRH10D60BT150NP-101MC","Sumida America Components Inc.","308-CDRH10D60BT150NP-101MCCT-ND","","","Cut Tape (CT)","Active","1","1,61000","1,61 €","500","Not Available","FIXED IND 100UH 2.3A 160MOHM SMD","ROHS3 Compliant","Not Available","Not Available"

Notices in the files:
parts and their libraries:
SparkFun-Connectors: Licensing: Creative Commons ShareAlike 4.0 International - https://creativecommons.org/licenses/by-sa/4.0
microbuilder: This work is placed in the public domain, and may be freely used for commercial and non-commercial work with the following conditions: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
